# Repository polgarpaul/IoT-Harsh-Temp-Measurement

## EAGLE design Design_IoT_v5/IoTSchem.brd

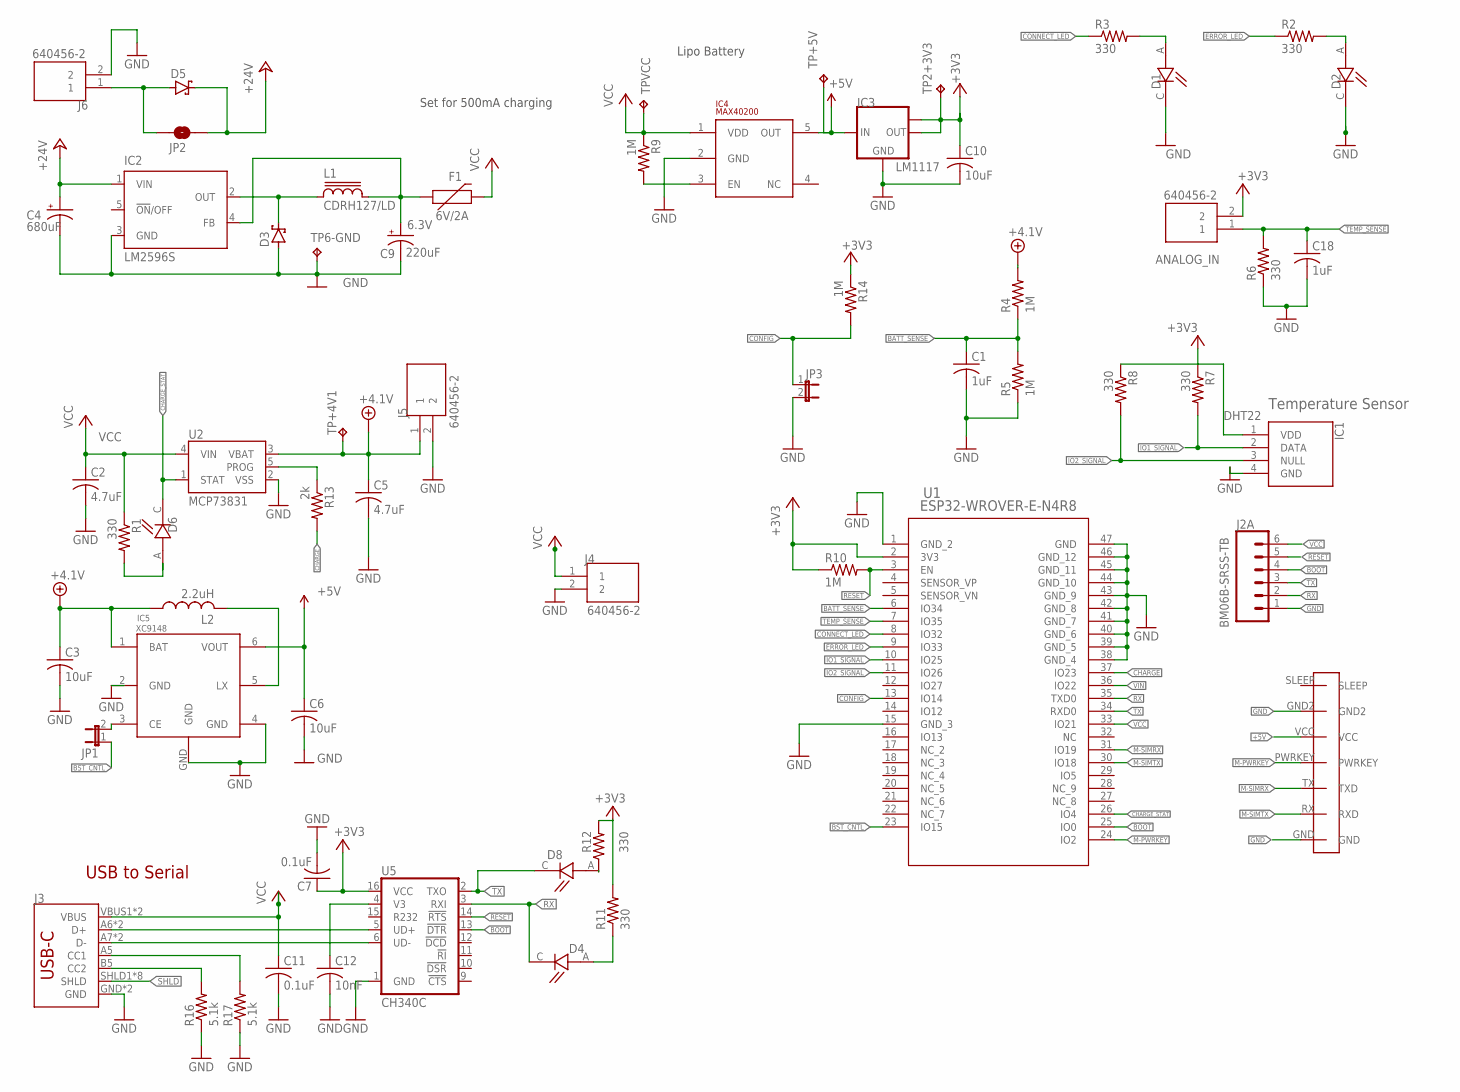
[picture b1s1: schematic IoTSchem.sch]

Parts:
ANALOG_IN: 640456-2; TE_640456-2
C1, C18: 1uF; C0805; DIGIKEYPART# 311-1365-1-ND
C2, C5: 4.7uF; C0805; DIGIKEYPART# 1276-6722-1-ND
C3, C6, C10: 10uF; C0805; DIGIKEYPART# 399-C0805C106K8PAC7800CT-ND
C4: 680uF; E5-10,5; VOLTAGE 25V
C7, C11: 0.1uF; C0805; DIGIKEYPART# 311-1140-1-ND
C9: 220uF; UD-6,3X5,8_NICHICON; VOLTAGE 6.3V
C12: 10nF; C0805; DIGIKEYPART# 1276-1015-1-ND
D1, D2, D4, D6, D8: 5988170107F; LEDC2012X70N
D3: SCHOTTKY-DIODESMD; SMB
D5: 1N4002; SMB
F1: 6V/2A; 1210
IC1: DHT22; DIGIKEYPART# 1528-1504-ND
IC2: LM2596S; TO263-5; DIGIKEYPART# 2156-LM2596SX-5.0/NOPB-ND
IC3: LM1117MPX-3.3; SOT223; DIGIKEYPART# LM1117IMP-3.3/NOPBCT-ND
IC4: MAX40200; SOT23-5
IC5: XC9148; USP-6C; DIGIKEYPART# 893-XC9148G50DER-GCT-ND
J1: SIM7000A
J2: BM06B-SRSS-TB; JST-6-SMD-HORI-1.0MM
J3: USB_C16PIN; USB-C-16P
J4, J5, J6: 640456-2; TE_640456-2
JP1, JP3: JP1E; JP1
JP2: JUMPER-SMT_2_NO_SILK; SMT-JUMPER_2_NO_SILK
L1: CDRH127/LD
L2: 2.2uH; L1812; DIGIKEYPART# 490-12049-1-ND
R1: 330; R0805
R2, R3, R6, R7, R8, R11, R12: 330; R0805; DIGIKEYPART# RMCF0805JT330RCT-ND
R4, R5, R9, R10, R14: 1M; R0805; DIGIKEYPART# RMCF0805JT1M00CT-ND
R13: 2k; R0805; DIGIKEYPART# RMCF0805FT2K00CT-ND
R16, R17: 5.1k; R0805; DIGIKEYPART# RMCF0805JT5K10CT-ND
TP2+3V3, TP6-GND: TPB1,27; B1,27
TP+4V1, TP+5V: TPB1,27; B1,27
TPVCC: TPB1,27; B1,27
U1: ESP32-WROVER-E-N4R8; ESP32­WROVER­E/ESP32­WROVER­IE
U2: MCP73831; SOT23-5; DIGIKEYPART# MCP73831T-2DCI/OTCT-ND
U5: CH340C; SO016

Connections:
+3V3: ANALOG_IN.2, C7.1, C10.1, IC1.1 (VDD), IC3.2 (OUT), IC3.TAB (OUT1), R7.1, R8.1, R10.1, R11.2, R12.2, R14.1, TP2+3V3.TP, U1.2 (3V3), U5.16 (VCC)
+4.1V: C3.1, C5.1, IC5.1 (BAT), J5.1, L2.1, R4.2, TP+4V1.TP, U2.3 (VBAT)
+5V: C6.1, IC3.3 (IN), IC4.5 (OUT), IC5.6 (VOUT), J1.VCC, TP+5V.TP
+24V: C4.+, D5.C, IC2.1 (VIN), JP2.2
BATT_SENSE: C1.1, R4.1, R5.2, U1.6 (IO34)
BOOT: J2.4, U1.25 (IO0), U5.13 (!DTR)
BST_CNTL: JP1.1, U1.23 (IO15)
CC1: J3.A5 (CC1), R17.2
CC2: J3.B5 (CC2), R16.2
CHARGE: R13.2, U1.37 (IO23)
CHARGE_STAT: D6.C, U1.26 (IO4), U2.1 (STAT)
CONFIG: JP3.1, R14.2, U1.13 (IO14)
CONNECT_LED: R3.1, U1.8 (IO32)
D+: J3.A6 (D+), J3.B6 (D+), U5.5 (UD+)
D-: J3.A7 (D-), J3.B7 (D-), U5.6 (UD-)
ERROR_LED: R2.1, U1.9 (IO33)
GND: C1.2, C2.2, C3.2, C4.-, C5.2, C6.2, C7.2, C9.-, C10.2, C11.2, C12.2, C18.2, D1.C, D2.C, D3.A, IC1.4 (GND), IC2.3 (GND), IC3.1 (GND), IC4.2 (GND), IC5.2 (GND), IC5.4 (GND), IC5.GND, J1.GND, J1.GND2, J2.1, J3.GND, J3.GND2 (GND), J4.2, J5.2, J6.2, JP3.2, R5.1, R6.1, R16.1, R17.1, TP6-GND.TP, U1.1 (GND_2), U1.15 (GND_3), U1.38 (GND_4), U1.39 (GND_5), U1.40 (GND_6), U1.41 (GND_7), U1.42 (GND_8), U1.43 (GND_9), U1.44 (GND_10), U1.45 (GND_11), U1.46 (GND_12), U1.47 (GND), U2.2 (VSS), U5.1 (GND)
IO1_SIGNAL: IC1.2 (DATA), R7.2, U1.10 (IO25)
IO2_SIGNAL: IC1.3 (NULL), R8.2, U1.11 (IO26)
M-PWRKEY: J1.PWRKEY, U1.24 (IO2)
M-SIMRX: J1.TX (TXD), U1.31 (IO19)
M-SIMTX: J1.RX (RXD), U1.30 (IO18)
N$: R13.1, U2.5 (PROG)
unnamed: D5.A, J6.1, JP2.1
unnamed: C12.1, U5.4 (V3)
unnamed: D6.A, R1.2
unnamed: IC5.5 (LX), L2.2
unnamed: D1.A, R3.2
unnamed: D2.A, R2.2
unnamed: IC4.3 (EN), R9.2
unnamed: C9.+, F1.1, IC2.4 (FB), L1.2
unnamed: D8.A, R12.1
unnamed: D4.A, R11.1
unnamed: IC5.3 (CE), JP1.2
OUT: D3.C, IC2.2 (OUT), L1.1
RESET: J2.5, R10.2, U1.3 (EN), U5.14 (!RTS)
RX: D4.C, J2.2, U1.35 (TXD0), U5.3 (RXI)
SHLD: J3.SHLD1 (SHLD), J3.SHLD2 (SHLD), J3.SHLD3 (SHLD), J3.SHLD4 (SHLD), J3.SHLD5 (SHLD), J3.SHLD6 (SHLD), J3.SHLD7 (SHLD), J3.SHLD8 (SHLD)
TEMP_SENSE: ANALOG_IN.1, C18.1, R6.2, U1.7 (IO35)
TX: D8.C, J2.3, U1.34 (RXD0), U5.2 (TXO)
VCC: C2.1, C11.1, F1.2, IC4.1 (VDD), J2.6, J3.VBUS1 (VBUS), J3.VBUS2 (VBUS), J4.1, R1.1, R9.1, TPVCC.TP, U1.33 (IO21), U2.4 (VIN)
VIN: U1.36 (IO22)

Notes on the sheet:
Temperature Sensor
Set for 500mA charging
Lipo Battery
USB to Serial

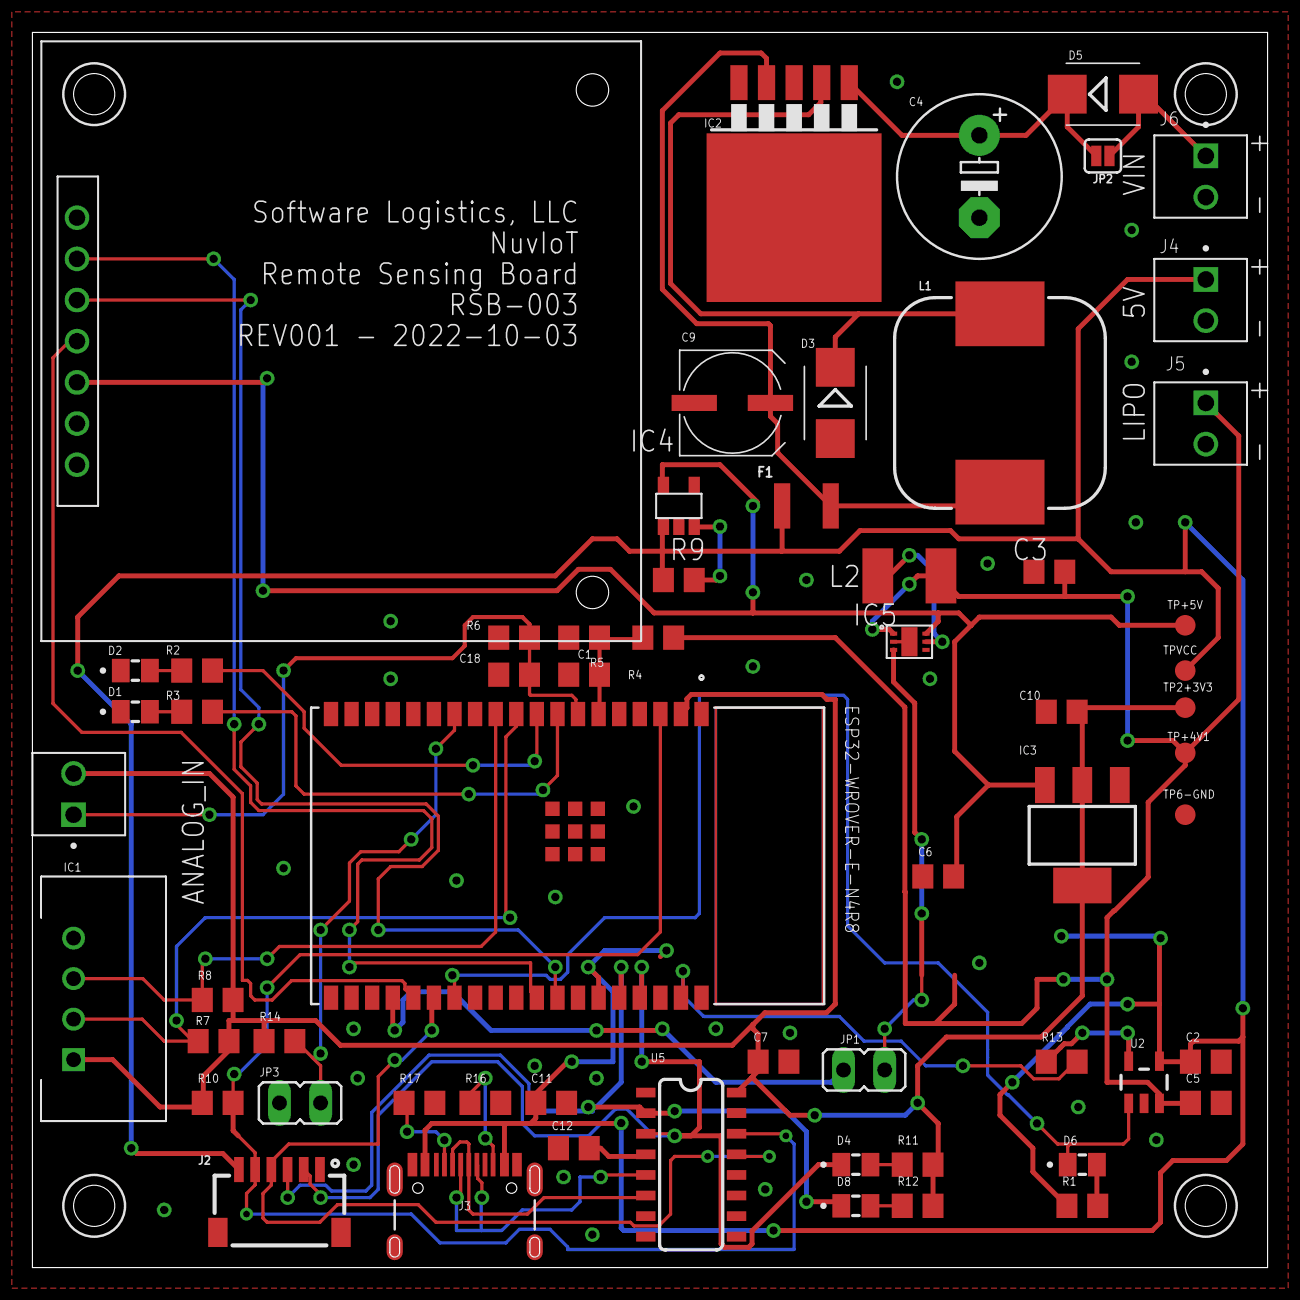
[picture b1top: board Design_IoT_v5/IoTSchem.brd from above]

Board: 2 copper layers, 76.2 x 76.2 mm, 61 parts (0 on the bottom side), 41 nets.

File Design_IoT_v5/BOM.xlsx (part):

Part | Value | Device | Package | Description | ARROW_PART_NUMBER | ARROW_PRICE-STOCK | COMMENT | COPYRIGHT | DESCRIPTION.1 | DIGI-KEY_PART_NUMBER | DIGI-KEY_PART_NUMBER_1 | DIGI-KEY_PART_NUMBER_2 | DIGI-KEY_PART_NUMBER_3 | DIGIKEYPART# | EU_ROHS_COMPLIANCE | HEIGHT | LM1117 | MANUFACTURER_NAME | MANUFACTURER_PART_NUMBER | MF | MFR_NAME | MOUSER_PART_NUMBER | MOUSER_PRICE-STOCK | MP | MPN | OC_FARNELL | OC_NEWARK | PACKAGE.1 | POPULARITY | PROD_ID | PURCHASE-URL | SPICEPREFIX | TP_SIGNAL_NAME | VALUE.1 | VOLTAGE | Column1
ANALOG_IN | 640456-2 | 640456-2 | TE_640456-2 | 220P MTA100 HDR ASSY SQ SPCL |  |  | 640456-2 |  | Connector Header Through Hole 2 position 0.100 (2.54mm) | A1921-ND |  |  |  |  | Compliant |  |  |  |  | TE Connectivity |  |  |  | 640456-2 |  |  |  | None |  |  | https://pricing.snapeda.com/search/part/640456-2/?ref=eda
C1 | 1uF | C-USC0805 | C0805 | CAPACITOR, American symbol |  |  |  |  |  |  |  |  |  | 311-1365-1-ND |  |  |  |  |  |  |  |  |  |  |  |  |  |  | 63 |  |  | C
C2 | 4.7uF | C-USC0805 | C0805 | CAPACITOR, American symbol |  |  |  |  |  |  |  |  |  | 1276-6722-1-ND |  |  |  |  |  |  |  |  |  |  |  |  |  |  | 63 |  |  | C
C3 | 4.7uF | C-USC0805 | C0805 | CAPACITOR, American symbol |  |  |  |  |  |  |  |  |  | 1276-6722-1-ND |  |  |  |  |  |  |  |  |  |  |  |  |  |  | 63 |  |  | C
C4 | 680uF | CPOL-USE5-10.5 | E5-10,5 | POLARIZED CAPACITOR, American symbol |  |  |  |  |  |  |  |  |  |  |  |  |  |  |  |  |  |  |  |  |  |  |  |  |  |  |  |  |  |  | 25V
C5 | 4.7uF | C-USC0805 | C0805 | CAPACITOR, American symbol |  |  |  |  |  |  |  |  |  | 1276-6722-1-ND |  |  |  |  |  |  |  |  |  |  |  |  |  |  | 63 |  |  | C
C6 | 10uF | C-USC0805 | C0805 | CAPACITOR, American symbol |  |  |  |  |  |  |  |  |  |  |  |  |  |  |  |  |  |  |  |  |  |  |  |  | 63 |  |  | C
C7 | 0.1uF | C-USC0805 | C0805 | CAPACITOR, American symbol |  |  |  |  |  |  |  |  |  | 311-1140-1-ND |  |  |  |  |  |  |  |  |  |  |  |  |  |  | 63 |  |  | C
C9 | 220uF | CPOL-USUD-6,3X5,8 | UD-6,3X5,8_NICHICON | POLARIZED CAPACITOR, American symbol |  |  |  |  |  |  |  |  |  |  |  |  |  |  |  |  |  |  |  |  |  |  |  |  |  |  |  |  |  |  | 6.3V
C10 | 10uF | C-USC0805 | C0805 | CAPACITOR, American symbol |  |  |  |  |  |  |  |  |  | 399-C0805C106K8PAC7800CT-ND |  |  |  |  |  |  |  |  |  |  |  |  |  |  | 63 |  |  | C
C11 | 0.1uF | C-USC0805 | C0805 | CAPACITOR, American symbol |  |  |  |  |  |  |  |  |  | 311-1140-1-ND |  |  |  |  |  |  |  |  |  |  |  |  |  |  | 63 |  |  | C
C12 | 10nF | C-USC0805 | C0805 | CAPACITOR, American symbol |  |  |  |  |  |  |  |  |  | 1276-1015-1-ND |  |  |  |  |  |  |  |  |  |  |  |  |  |  | 63 |  |  | C
C18 | 1uF | C-USC0805 | C0805 | CAPACITOR, American symbol |  |  |  |  |  |  |  |  |  | 311-1365-1-ND |  |  |  |  |  |  |  |  |  |  |  |  |  |  | 63 |  |  | C
D1 | 5988170107F | 5988170107F | LEDC2012X70N | Standard LEDs - SMD Green Water Clr 40mcd 570nm |  |  |  |  | Green 566nm LED Indication - Discrete 2V 0805 (2012 Metric) | 350-2044-1-ND |  |  |  |  |  |  |  |  |  | Dialight |  |  |  | 5988170107F |  |  |  | 0805 Dialight |  |  | https://pricing.snapeda.com/search/part/5988170107F/?ref=eda
D2 | 5988170107F | 5988170107F | LEDC2012X70N | Standard LEDs - SMD Green Water Clr 40mcd 570nm |  |  |  |  | Green 566nm LED Indication - Discrete 2V 0805 (2012 Metric) | 350-2044-1-ND |  |  |  |  |  |  |  |  |  | Dialight |  |  |  | 5988170107F |  |  |  | 0805 Dialight |  |  | https://pricing.snapeda.com/search/part/5988170107F/?ref=eda
D3 |  | SCHOTTKY-DIODESMD | SMB | Schottky Diode |  |  |  |  |  |  |  |  |  |  |  |  |  |  |  |  |  |  |  |  |  |  |  |  | 2
D4 | 5988170107F | 5988170107F | LEDC2012X70N | Standard LEDs - SMD Green Water Clr 40mcd 570nm |  |  |  |  | Green 566nm LED Indication - Discrete 2V 0805 (2012 Metric) | 350-2044-1-ND |  |  |  |  |  |  |  |  |  | Dialight |  |  |  | 5988170107F |  |  |  | 0805 Dialight |  |  | https://pricing.snapeda.com/search/part/5988170107F/?ref=eda
D5 | 1N4002 | SCHOTTKY-DIODESMD | SMB | Schottky Diode |  |  |  |  |  |  |  |  |  |  |  |  |  |  |  |  |  |  |  |  |  |  |  |  | 2
D6 | 5988170107F | 5988170107F | LEDC2012X70N | Standard LEDs - SMD Green Water Clr 40mcd 570nm |  |  |  |  | Green 566nm LED Indication - Discrete 2V 0805 (2012 Metric) | 350-2044-1-ND |  |  |  |  |  |  |  |  |  | Dialight |  |  |  | 5988170107F |  |  |  | 0805 Dialight |  |  | https://pricing.snapeda.com/search/part/5988170107F/?ref=eda
D7 | 1N4002 | SCHOTTKY-DIODESMD | SMB | Schottky Diode |  |  |  |  |  |  |  |  |  |  |  |  |  |  |  |  |  |  |  |  |  |  |  |  | 2
D8 | 5988170107F | 5988170107F | LEDC2012X70N | Standard LEDs - SMD Green Water Clr 40mcd 570nm |  |  |  |  | Green 566nm LED Indication - Discrete 2V 0805 (2012 Metric) | 350-2044-1-ND |  |  |  |  |  |  |  |  |  | Dialight |  |  |  | 5988170107F |  |  |  | 0805 Dialight |  |  | https://pricing.snapeda.com/search/part/5988170107F/?ref=eda
F1 | 6V/2A | PPTC_6V2A | 1210 | Resettable Fuse PPTC |  |  |  |  |  |  |  |  |  |  |  |  |  |  |  |  |  |  |  |  |  |  |  |  |  | RES-14313 |  |  |  | 6V/2A
IC1 | DHT22 | DHT22 | DHT22 | Digital-output relative humidity & temperature sensor/module DHT22 |  |  |  |  | Digital-output relative humidity & temperature sensor/module DHT22 |  |  |  |  | 1528-1504-ND |  | 25.1mm |  | Aosong Electronics | DHT22
IC2 | LM2596S | LM2596S | TO263-5 | SIMPLE SWITCHER® Power Converter 150 kHz 3A Step-Down Voltage Regulator |  |  |  |  |  |  |  |  |  | 2156-LM2596SX-5.0/NOPB-ND |  |  |  |  |  | NATIONAL SEMICONDUCTOR |  |  |  |  | LM2596S-ADJ/NOPB | 9494367 | 41K3842 |  | 12
IC3 |  | LM1117MPX-3.3 | SOT223 |  |  |  |  |  |  |  |  |  |  | LM1117IMP-3.3/NOPBCT-ND
IC4 |  | XC9140 | SOT-25 |  |  |  |  |  |  |  |  |  |  | 893-1181-1-ND
J1 | SIM7000A | SIM7000A | SIM7000A
J2 | BM06B-SRSS-TB | JST_6_PIN_HORIZONTAL | JST-6-SMD-HORI-1.0MM | JST 6 pin horizontal connector |  |  |  |  |  |  |  |  |  |  |  |  |  |  |  |  |  |  |  |  |  |  |  |  |  | XXX-00000 |  |  |  | BM06B-SRSS-TB
J3 |  | USB_C16PIN | USB-C-16P | USB Type C 16Pin Connector |  |  |  |  |  |  |  |  |  |  |  |  |  |  |  |  |  |  |  |  |  |  |  |  |  | CONN-14122
J4 | 640456-2 | 640456-2 | TE_640456-2 | 220P MTA100 HDR ASSY SQ SPCL |  |  | 640456-2 |  | Connector Header Through Hole 2 position 0.100 (2.54mm) | A1921-ND |  |  |  |  | Compliant |  |  |  |  | TE Connectivity |  |  |  | 640456-2 |  |  |  | None |  |  | https://pricing.snapeda.com/search/part/640456-2/?ref=eda
J5 | 640456-2 | 640456-2 | TE_640456-2 | 220P MTA100 HDR ASSY SQ SPCL |  |  | 640456-2 |  | Connector Header Through Hole 2 position 0.100 (2.54mm) | A1921-ND |  |  |  |  | Compliant |  |  |  |  | TE Connectivity |  |  |  | 640456-2 |  |  |  | None |  |  | https://pricing.snapeda.com/search/part/640456-2/?ref=eda
J6 | 640456-2 | 640456-2 | TE_640456-2 | 220P MTA100 HDR ASSY SQ SPCL |  |  | 640456-2 |  | Connector Header Through Hole 2 position 0.100 (2.54mm) | A1921-ND |  |  |  |  | Compliant |  |  |  |  | TE Connectivity |  |  |  | 640456-2 |  |  |  | None |  |  | https://pricing.snapeda.com/search/part/640456-2/?ref=eda
JP1 |  | JP1E | JP1 | JUMPER |  |  |  |  |  |  |  |  |  |  |  |  |  |  |  |  |  |  |  |  |  |  |  |  | 61
JP2 | JUMPER-SMT_2_NO_SILK | JUMPER-SMT_2_NO_SILK | SMT-JUMPER_2_NO_SILK | Normally open jumper
JP3 |  | JP1E | JP1 | JUMPER |  |  |  |  |  |  |  |  |  |  |  |  |  |  |  |  |  |  |  |  |  |  |  |  | 61
L1 | CDRH127/LD | CDRH127/LD | CDRH127/LD | Power Inductor
L2 | 4.7uH | L-USL2825P | L2825P | INDUCTOR, American symbol |  |  |  |  |  |  |  |  |  |  |  |  |  |  |  |  |  |  |  |  |  |  |  |  | 3 |  |  | L
R1 | 330 | R-US_R0805 | R0805 | RESISTOR, American symbol |  |  |  |  |  |  |  |  |  |  |  |  |  |  |  |  |  |  |  |  |  |  |  |  | 85 |  |  | R
R2 | 330 | R-US_R0805 | R0805 | RESISTOR, American symbol |  |  |  |  |  |  |  |  |  | RMCF0805JT330RCT-ND |  |  |  |  |  |  |  |  |  |  |  |  |  |  | 85 |  |  | R
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
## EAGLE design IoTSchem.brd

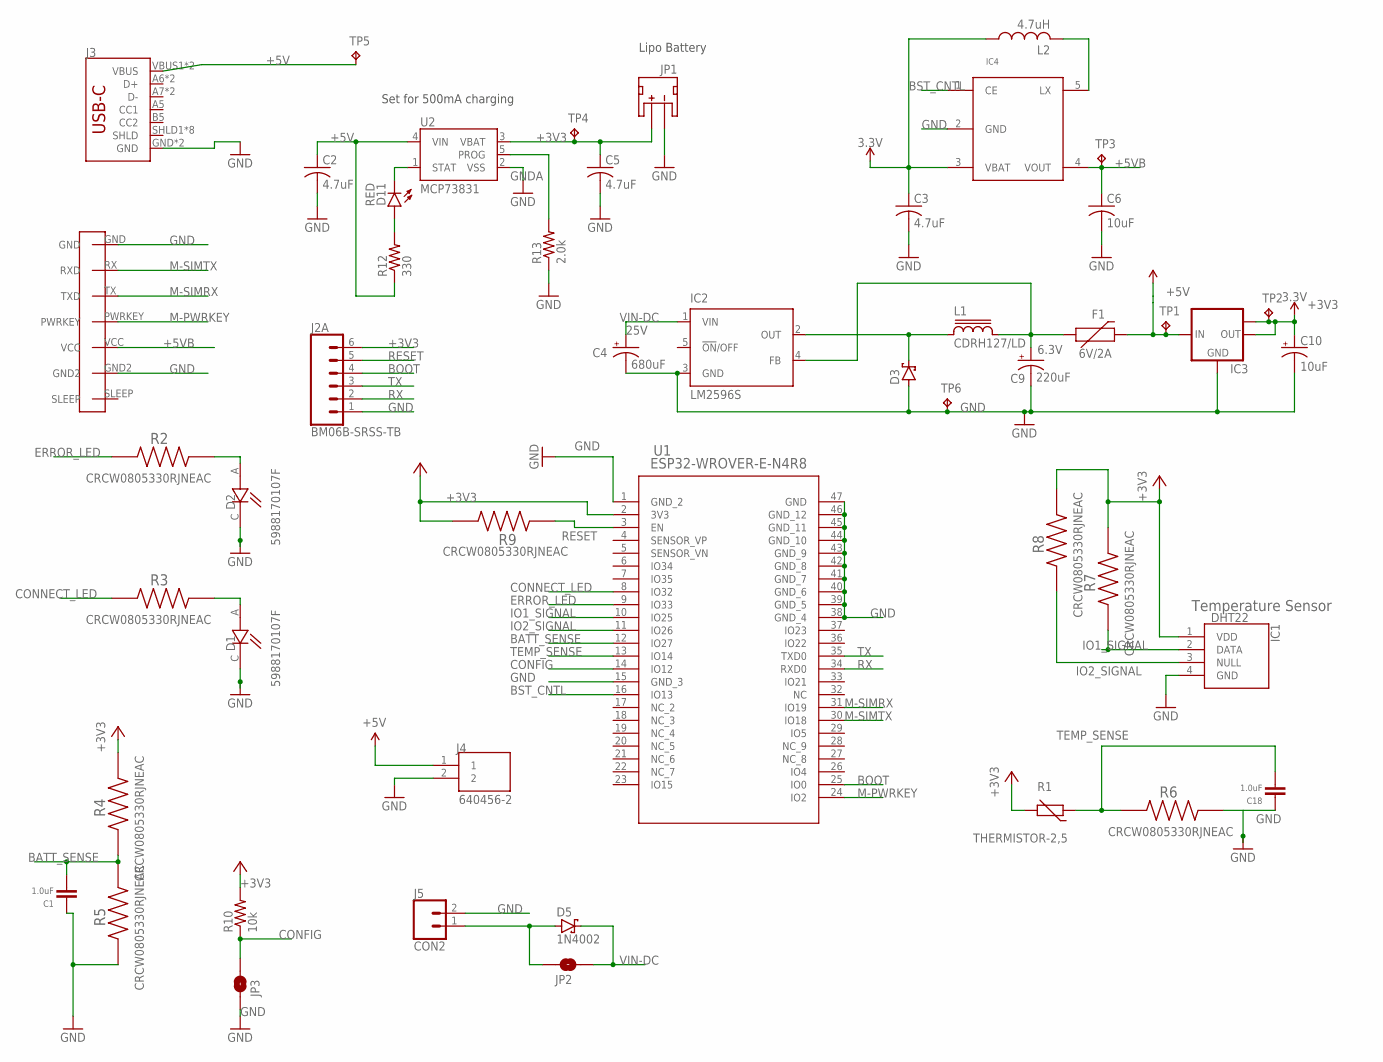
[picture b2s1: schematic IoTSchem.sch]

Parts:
C1, C18: 1.0uF; 0805
C2, C5: 4.7uF; C0603
C3: 4.7uF; C0805
C4: 680uF; E5-10,5; VOLTAGE 25V
C6: 10uF; C0805
C9: 220uF; UD-6,3X5,8_NICHICON; VOLTAGE 6.3V
C10: 10uF; EIA3216
D1, D2: 5988170107F; LEDC2012X70N
D3: SCHOTTKY-DIODESMD; SMB
D5: 1N4002; SMB
D11: RED; LED-0603
F1: 6V/2A; 1210
IC1: DHT22
IC2: LM2596S; TO263-5
IC3: LM1117MPX-3.3; SOT223
IC4: XC9140; SOT-25
J1: SIM7000A
J2: BM06B-SRSS-TB; JST-6-SMD-HORI-1.0MM
J3: USB_C2-LAYER; USB-C-16P
J4: 640456-2; TE_640456-2
J5: CON2; 1X02
JP1: JST; JST-2-SMD
JP2, JP3: JUMPER-SMT_2_NO_SILK; SMT-JUMPER_2_NO_SILK
L1: CDRH127/LD
L2: 4.7uH; L2825P
R1: THERMISTOR-2,5; RS-2,5
R2, R3, R4, R5, R6, R7, R8, R9: CRCW0805330RJNEAC; RESC2012X60N
R10: 10k; R0603
R12: 330; R0603
R13: 2.0k; R0603
TP1, TP2, TP3, TP4, TP5, TP6: TPB1,27; B1,27
U1: ESP32-WROVER-E-N4R8; ESP32­WROVER­E/ESP32­WROVER­IE
U2: MCP73831; SOT23-5

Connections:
3.3V: C3.1, IC4.3 (VBAT), L2.1
+3V3: C5.1, C10.+, IC1.1 (VDD), IC3.2 (OUT), IC3.TAB (OUT1), J2.6, JP1.2 (+), R1.2, R4.2, R7.2, R8.2, R9.2, R10.2, TP2.TP, TP4.TP, U1.2 (3V3), U2.3 (VBAT)
+5V: C2.1, F1.2, IC3.3 (IN), J3.VBUS1 (VBUS), J3.VBUS2 (VBUS), J4.1, R12.1, TP1.TP, TP5.TP, U2.4 (VIN)
+5VB: C6.1, IC4.4 (VOUT), J1.VCC, TP3.TP
BATT_SENSE: C1.2, R4.1, R5.2, U1.12 (IO27)
BOOT: J2.4, U1.25 (IO0)
BST_CNTL: IC4.1 (CE), U1.16 (IO13)
CONFIG: JP3.2, R10.1, U1.14 (IO12)
CONNECT_LED: R3.1, U1.8 (IO32)
ERROR_LED: R2.1, U1.9 (IO33)
GND: C1.1, C2.2, C3.2, C4.-, C5.2, C6.2, C9.-, C10.-, C18.1, D1.C, D2.C, D3.A, IC1.4 (GND), IC2.3 (GND), IC3.1 (GND), IC4.2 (GND), J1.GND, J1.GND2, J2.1, J3.GND, J3.GND2 (GND), J4.2, J5.2, JP1.1 (-), JP3.1, R5.1, R6.2, R13.1, TP6.TP, U1.1 (GND_2), U1.15 (GND_3), U1.38 (GND_4), U1.39 (GND_5), U1.40 (GND_6), U1.41 (GND_7), U1.42 (GND_8), U1.43 (GND_9), U1.44 (GND_10), U1.45 (GND_11), U1.46 (GND_12), U1.47 (GND)
GNDA: U2.2 (VSS)
IO1_SIGNAL: IC1.2 (DATA), R7.1, U1.10 (IO25)
IO2_SIGNAL: IC1.3 (NULL), R8.1, U1.11 (IO26)
M-PWRKEY: J1.PWRKEY, U1.24 (IO2)
M-SIMRX: J1.TX (TXD), U1.31 (IO19)
M-SIMTX: J1.RX (RXD), U1.30 (IO18)
unnamed: D5.A, J5.1, JP2.1
unnamed: D11.A, R12.2
unnamed: IC4.5 (LX), L2.2
unnamed: D1.A, R3.2
unnamed: D2.A, R2.2
unnamed: C9.+, F1.1, IC2.4 (FB), L1.2
OUT: D3.C, IC2.2 (OUT), L1.1
PROG: R13.2, U2.5 (PROG)
RESET: J2.5, R9.1, U1.3 (EN)
RX: J2.2, U1.34 (RXD0)
STAT: D11.C, U2.1 (STAT)
TEMP_SENSE: C18.2, R1.1, R6.1, U1.13 (IO14)
TX: J2.3, U1.35 (TXD0)
VIN-DC: C4.+, D5.C, IC2.1 (VIN), JP2.2

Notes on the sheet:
Temperature Sensor
Set for 500mA charging
Lipo Battery

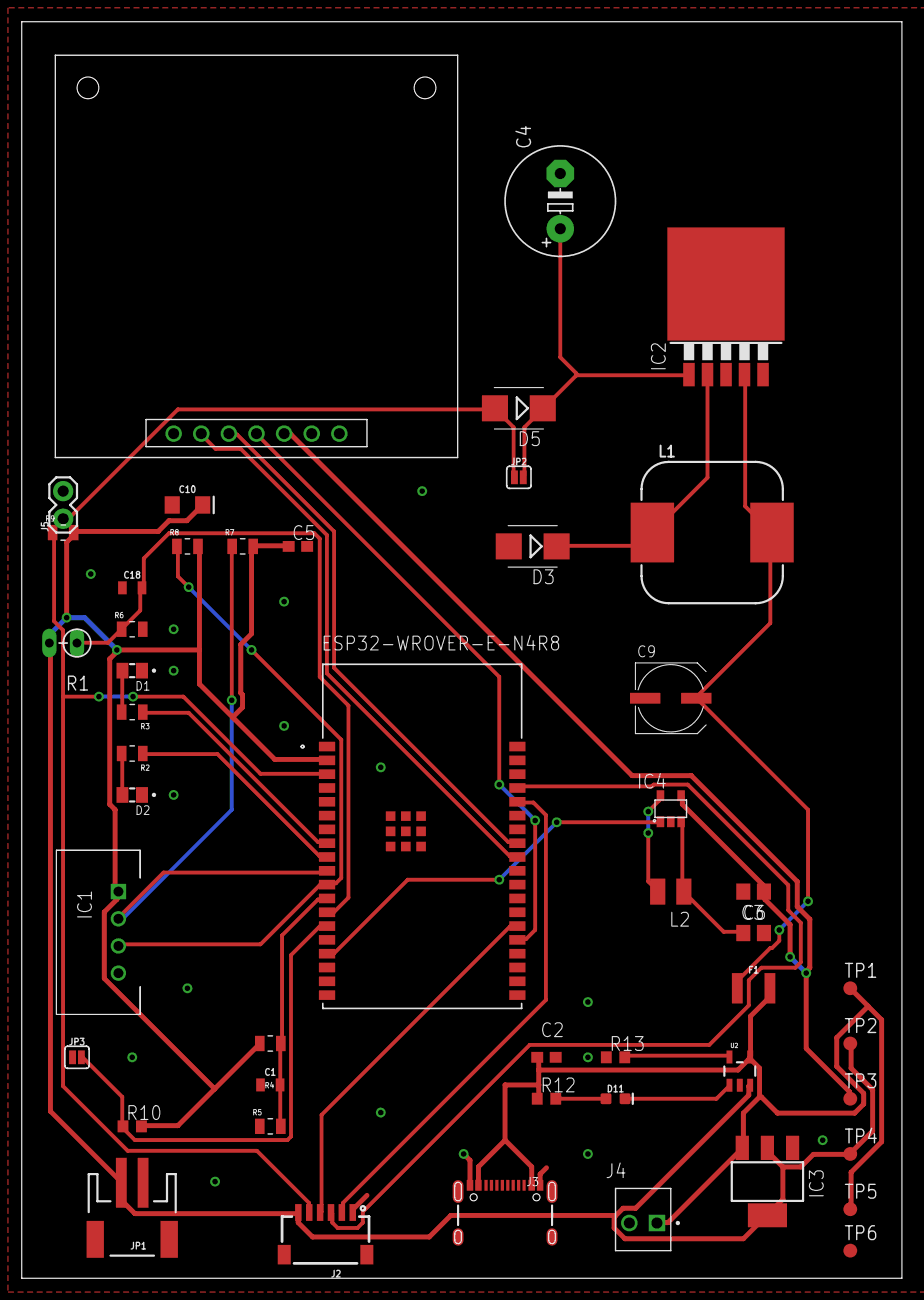
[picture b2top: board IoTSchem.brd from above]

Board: 2 copper layers, 80.9 x 115.6 mm, 49 parts (0 on the bottom side), 30 nets.

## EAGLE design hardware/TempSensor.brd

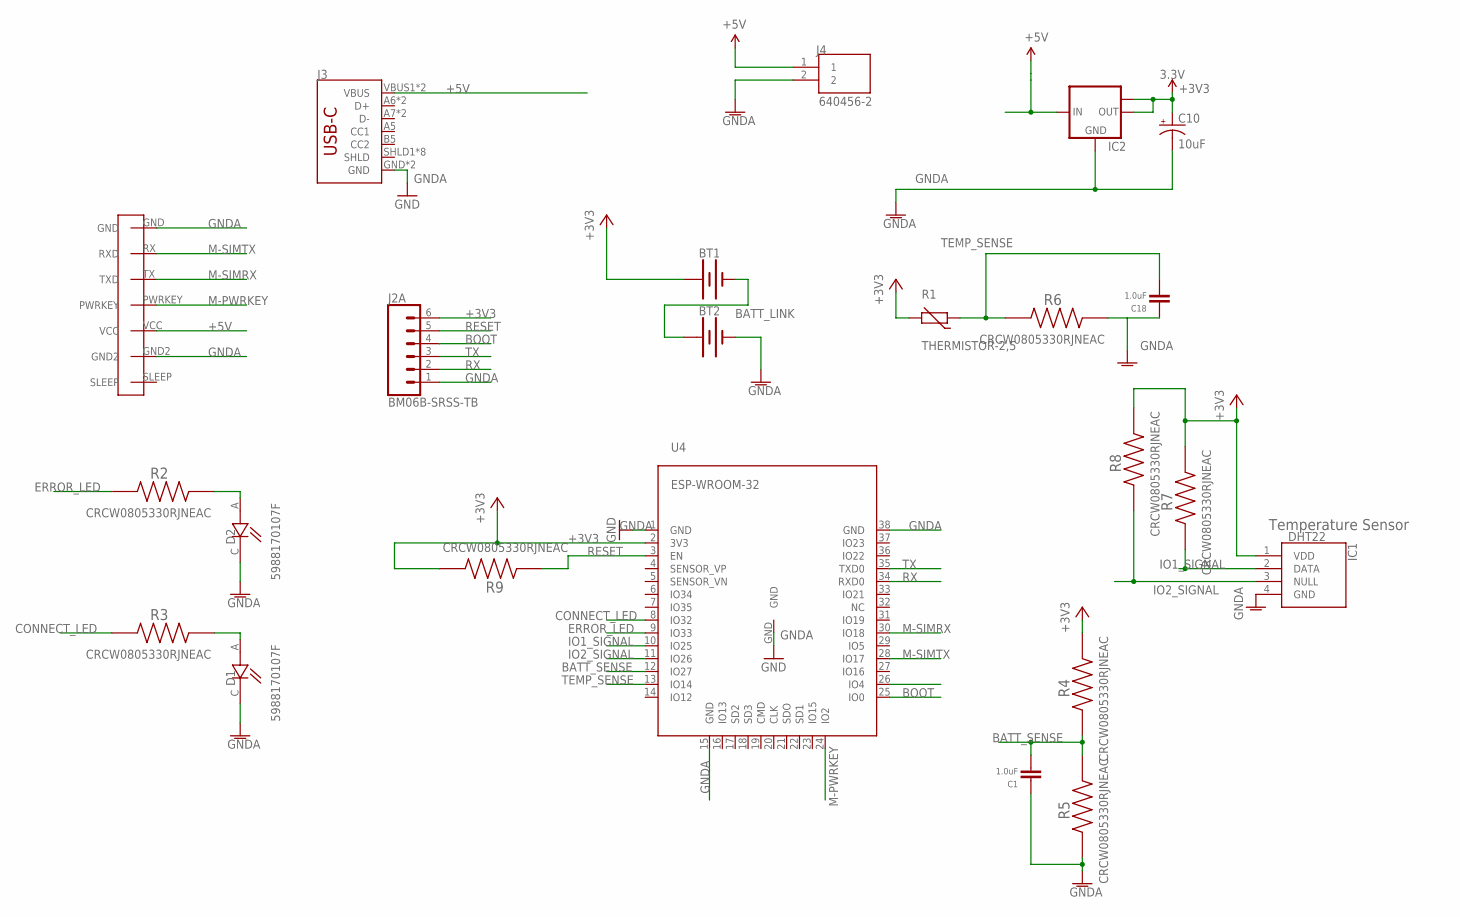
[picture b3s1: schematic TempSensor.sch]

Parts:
BT1, BT2: BATTERY-AA
C1, C18: 1.0uF; 0805
C10: 10uF; EIA3216
D1, D2: 5988170107F; LEDC2012X70N
IC1: DHT22
IC2: LM1117MPX-3.3; SOT223
J1: SIM7000A
J2: BM06B-SRSS-TB; JST-6-SMD-HORI-1.0MM
J3: USB_C16PIN; USB-C-16P
J4: 640456-2; TE_640456-2
R1: THERMISTOR-2,5; RS-2,5
R2, R3, R4, R5, R6, R7, R8, R9: CRCW0805330RJNEAC; RESC2012X60N
U4: ESP-WROOM-32

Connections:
+3V3: BT1.PWR@1 (+), C10.+, IC1.1 (VDD), IC2.2 (OUT), IC2.TAB (OUT1), J2.6, R1.2, R4.2, R7.2, R8.2, R9.2, U4.2 (3V3)
+5V: IC2.3 (IN), J1.VCC, J3.VBUS1 (VBUS), J3.VBUS2 (VBUS), J4.1
BATT_LINK: BT1.GND@1 (-), BT2.PWR@1 (+)
BATT_SENSE: C1.2, R4.1, R5.2, U4.12 (IO27)
BOOT: J2.4, U4.25 (IO0)
CONNECT_LED: R3.1, U4.8 (IO32)
ERROR_LED: R2.1, U4.9 (IO33)
GNDA: BT2.GND@1 (-), C1.1, C10.-, C18.1, D1.C, D2.C, IC1.4 (GND), IC2.1 (GND), J1.GND, J1.GND2, J2.1, J3.GND, J3.GND2 (GND), J4.2, R5.1, R6.2, U4.1 (GND), U4.15 (GND), U4.38 (GND), U4.GND
IO1_SIGNAL: IC1.2 (DATA), R7.1, U4.10 (IO25)
IO2_SIGNAL: IC1.3 (NULL), R8.1, U4.11 (IO26)
M-PWRKEY: J1.PWRKEY, U4.24 (IO2)
M-SIMRX: J1.TX (TXD), U4.30 (IO18)
M-SIMTX: J1.RX (RXD), U4.28 (IO17)
unnamed: D1.A, R3.2
unnamed: D2.A, R2.2
RESET: J2.5, R9.1, U4.3 (EN)
RX: J2.2, U4.34 (RXD0)
TEMP_SENSE: C18.2, R1.1, R6.1, U4.13 (IO14)
TX: J2.3, U4.35 (TXD0)

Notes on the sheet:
Temperature Sensor

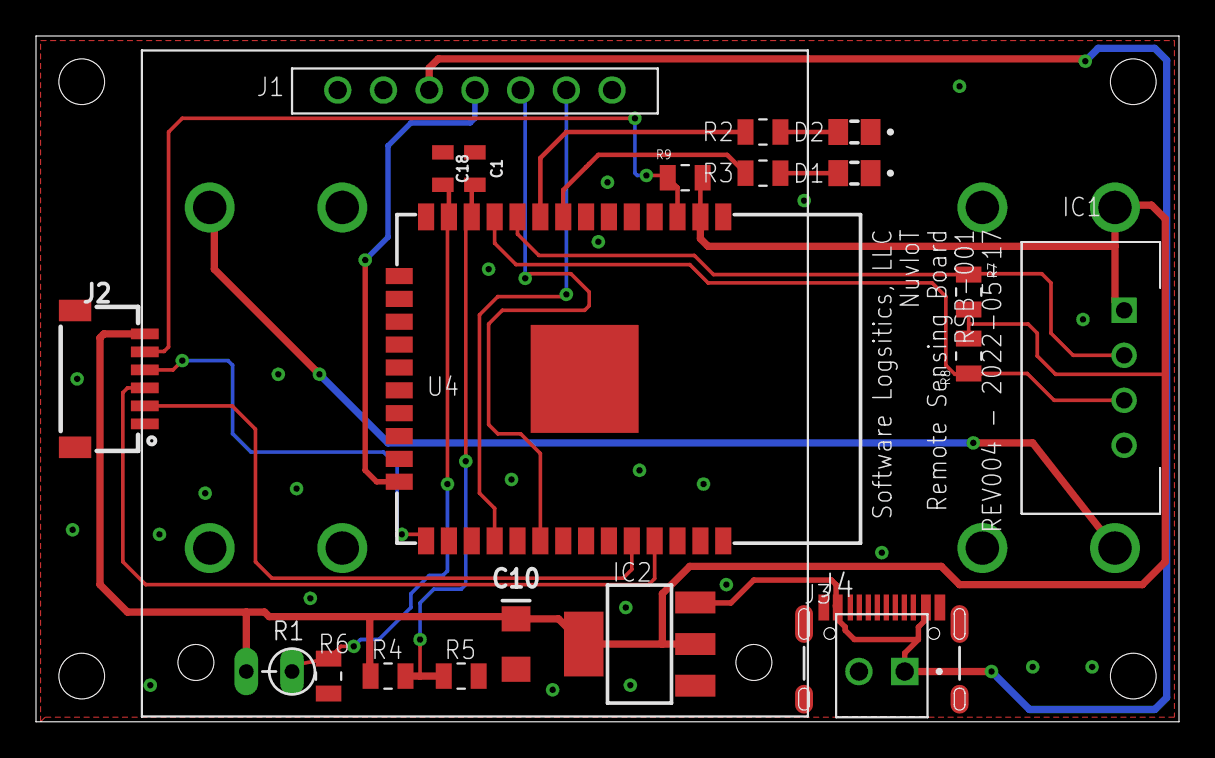
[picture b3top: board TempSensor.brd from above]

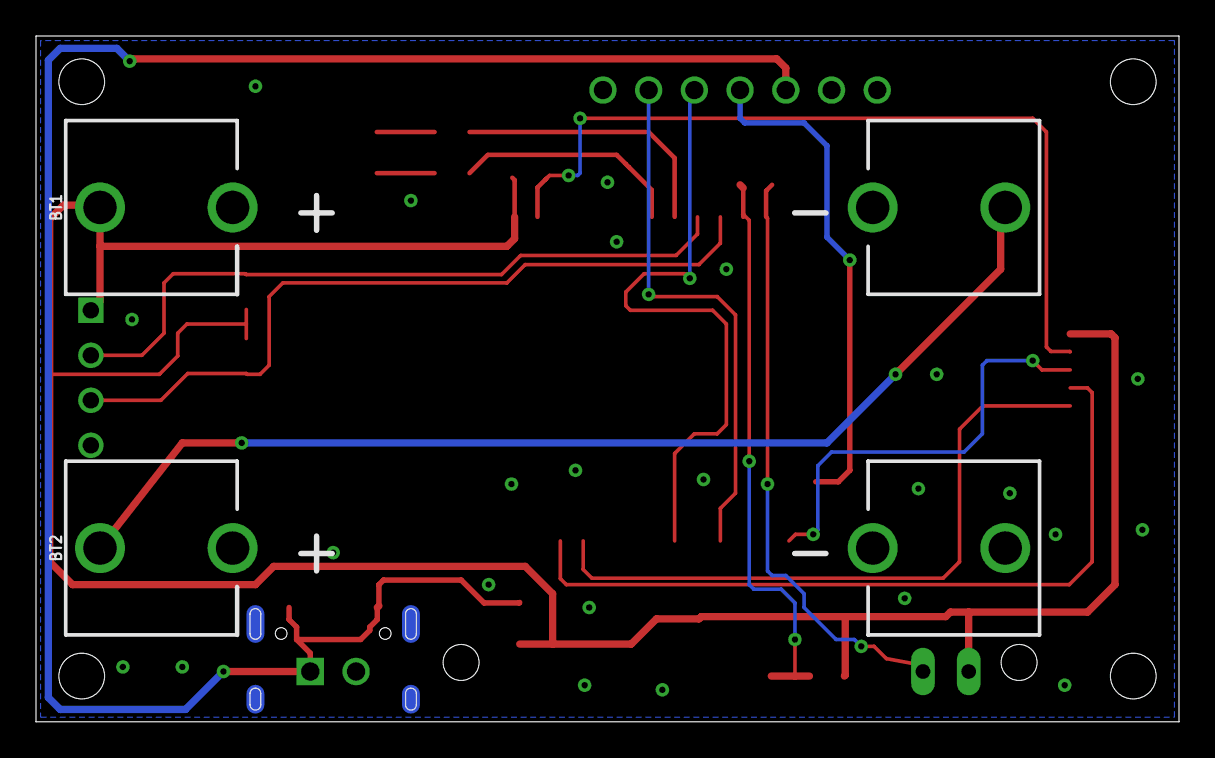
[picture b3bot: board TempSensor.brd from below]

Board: 2 copper layers, 63.5 x 38.1 mm, 23 parts (2 on the bottom side), 19 nets.

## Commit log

2022-07-18 Create IOT
2022-07-25 initial board add
2022-07-25 add firmware
2022-07-28 add mobile app project
2022-09-12 Create New Board
2022-09-26 board layout
2022-10-03 as sent to board house
2022-10-26 For review

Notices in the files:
parts and their libraries:
SparkFun-Aesthetics: Licensing: Creative Commons ShareAlike 4.0 International - https://creativecommons.org/licenses/by-sa/4.0
ESP32WROVER: COPYRIGHT: Copyright (C) 2022 Ultra Librarian. All rights reserved.
inductor-sumida: Copyright (C) 2008, Bob Starr
